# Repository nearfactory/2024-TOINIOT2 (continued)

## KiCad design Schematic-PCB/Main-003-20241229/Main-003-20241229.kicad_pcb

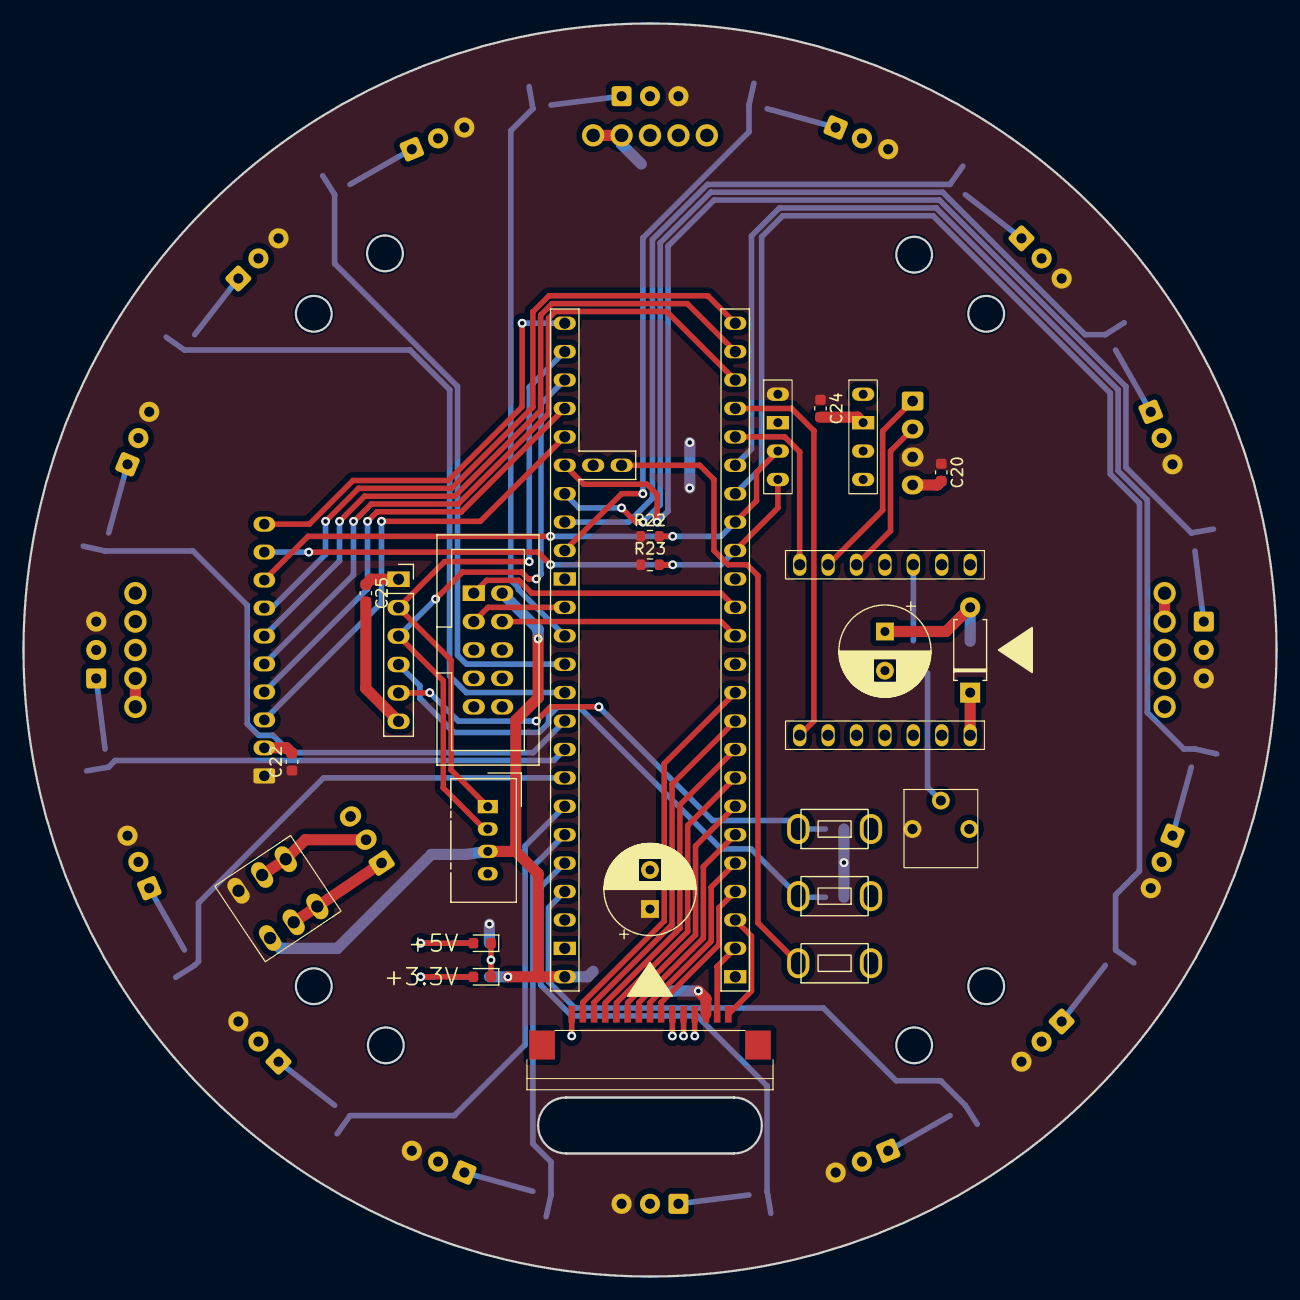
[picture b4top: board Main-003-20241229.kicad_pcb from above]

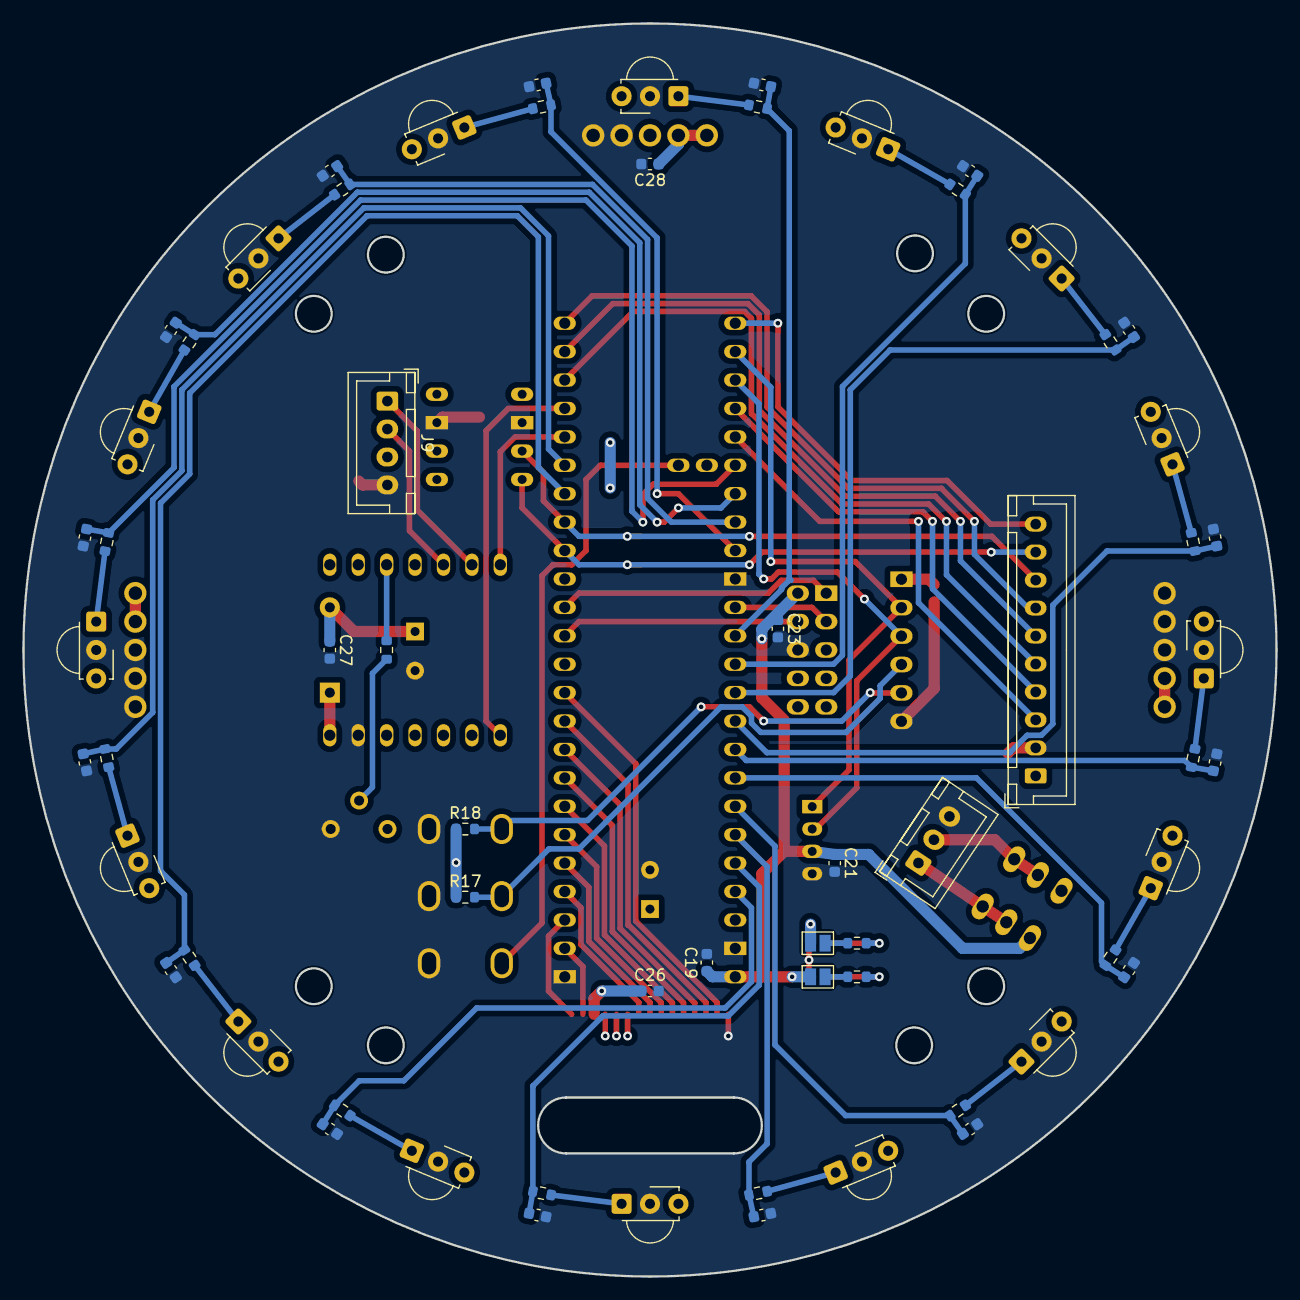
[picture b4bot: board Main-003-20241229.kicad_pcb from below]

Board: 2 copper layers, 112.0 x 112.0 mm, 90 parts (64 on the bottom side), 78 nets.

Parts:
C1, C2, C3, C4, C5, C6, C7, C8, C9, C10, C11, C12, C13, C14, C15, C16: 0.33uF; C_0603_1608Metric
C17, C18: 470uF; CP_Radial_D8.0mm_P3.50mm
C19, C20, C21, C22, C23, C24, C25, C26, C27, C28: 0.1uF; C_0603_1608Metric
D1: PWR-5; LED_0603_1608Metric
D2: PWR-3.3; LED_0603_1608Metric
D3: D_Small; D_A-405_P7.62mm_Horizontal
J1: Conn_PWR; JST_XH_B3B-XH-A_1x03_P2.50mm_Vertical
J2, J3, J4: Conn_NeoPixel; Connector
J5: CamS3-6; PinSocket_1x06_P2.54mm_Vertical
J6: CamS3-4; NS-Tech_Grove_1x04_P2mm_Vertical
J7: Pixy 2.1; IDC-Header_2x05_P2.54mm_Vertical
J8: Conn_MD; 1.0K-FX-15PWB
J9: Conn_Dribbler; JST_XH_B4B-XH-A_1x04_P2.50mm_Vertical
J10: Conn_UI; JST_XH_B10B-XH-A_1x10_P2.50mm_Vertical
JP1, JP2: Jumper_2_Small_Open; SolderJumper-2_P1.3mm_Open_Pad1.0x1.5mm
R1, R2, R3, R4, R5, R6, R7, R8, R9, R10, R11, R12, R13, R14, R15, R16: 39K; R_0603_1608Metric
R17, R18, R21: 10K; R_0603_1608Metric
R19, R20: 330; R_0603_1608Metric
R22, R23: 1K; R_0603_1608Metric
RV1: 10K; 3362P
SW1: Main_RST; TVBP06-B043C
SW2, SW3: Cam_RST; TVBP06-B043C
SW4: SW_DPDT_x2; 2MD1-T2-B4-M2-Q-N
U1, U2, U3, U4, U5, U6, U7, U8, U9, U10, U11, U12, U13, U14, U15, U16: TSSP4038
U17: DEV-16771; MODULE_DEV-16771
U18: BNO055
U19: XIAO ESP32C3

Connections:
3.3V: J1.2, SW4.5 (B), SW4.6 (C)
5.0V: J1.1, SW4.2 (B), SW4.3 (C)
+3.3V: C18.1, C20.1, C22.1, C24.1, C26.1, J8.13, J9.3, J10.1, JP2.2 (B), R17.1, R18.1, R22.1, R23.1, RV1.1, SW4.4 (A), U1.3 (Vs), U2.3 (Vs), U3.3 (Vs), U4.3 (Vs), U5.3 (Vs), U6.3 (Vs), U7.3 (Vs), U8.3 (Vs), U9.3 (Vs), U10.3 (Vs), U11.3 (Vs), U12.3 (Vs), U13.3 (Vs), U14.3 (Vs), U15.3 (Vs), U16.3 (Vs), U18.1 (VIN)
+5V: C17.1, C19.1, C21.1, C23.1, C25.1, C27.1, C28.1, D3.2 (A), J2.1, J2.2, J3.1, J3.2, J4.1, J4.2, J5.1, J6.3, J7.2, JP1.2 (B), SW4.1 (A), U17.VIN
BUZZER: J10.10, U17.33 (MCLK2)
Cam-RX: J5.3, J6.2, U17.35 (TX8)
Cam-TX: J5.2, J6.1, U17.34 (RX8)
Cam_EN: J5.4, R17.2, SW2.2
Cam_G0: J5.5, R18.2, SW3.2
EN-1: J8.2, U17.9 (OUT1C)
EN-2: J8.4, U17.7 (RX2)
EN-3: J8.6, U17.5 (IN2)
EN-4: J8.8, U17.3 (LRCLK2)
EN-D: J9.2, U19.5 (SDA_D4)
GND: C1.2, C2.2, C3.2, C4.2, C5.2, C6.2, C7.2, C8.2, C9.2, C10.2, C11.2, C12.2, C13.2, C14.2, C15.2, C16.2, C17.2, C18.2, C19.2, C20.2, C21.2, C22.2, C23.2, C24.2, C25.2, C26.2, C27.2, C28.2, D1.1 (K), D2.1 (K), J1.3, J2.4, J2.5, J3.3, J3.4, J3.5, J4.3, J4.4, J4.5, J5.6, J6.4, J7.6, J8.1, J9.4, J10.2, RV1.3, SW1.1, SW2.1, SW3.1, U1.2 (GND), U2.2 (GND), U3.2 (GND), U4.2 (GND), U5.2 (GND), U6.2 (GND), U7.2 (GND), U8.2 (GND), U9.2 (GND), U10.2 (GND), U11.2 (GND), U12.2 (GND), U13.2 (GND), U14.2 (GND), U15.2 (GND), U16.2 (GND), U17.GND, U18.2 (GND), U18.7 (GND), U19.13 (GND)
KickerSignal: J8.11, U19.4 (A3_D3)
Line-RX: J8.15, U17.1 (TX1)
Line-TX: J8.14, U17.0 (RX1)
MISO: J7.1, U17.12 (MISO)
MOSI: J7.4, U17.11 (MOSI)
Main-RX7: U17.28 (RX7), U19.7 (TX_D6)
Main-TX7: U17.29 (TX7), U19.8 (RX_D7)
Main_RST: SW1.2, U17.PROGRAM
NeoPixel_PWM: J2.3, U19.11 (MOSI_D10)
unnamed: D1.2 (A), R19.2
unnamed: D2.2 (A), R20.2
unnamed: D3.1 (K), U19.14 (5V)
unnamed: JP1.1 (A), R19.1
unnamed: JP2.1 (A), R20.1
unnamed: R21.1, RV1.2
unnamed: R1.1, U1.1 (OUT)
unnamed: R2.1, U2.1 (OUT)
unnamed: R3.1, U3.1 (OUT)
unnamed: R4.1, U4.1 (OUT)
unnamed: R5.1, U5.1 (OUT)
unnamed: R6.1, U6.1 (OUT)
unnamed: R7.1, U7.1 (OUT)
unnamed: R8.1, U8.1 (OUT)
unnamed: R9.1, U9.1 (OUT)
unnamed: R10.1, U10.1 (OUT)
unnamed: R11.1, U11.1 (OUT)
unnamed: R12.1, U12.1 (OUT)
unnamed: R13.1, U13.1 (OUT)
unnamed: R14.1, U14.1 (OUT)
unnamed: R15.1, U15.1 (OUT)
unnamed: R16.1, U16.1 (OUT)
PH-1: J8.3, U17.8 (TX2)
PH-2: J8.5, U17.6 (OUT1D)
PH-3: J8.7, U17.4 (BCLK2)
PH-4: J8.9, U17.2 (OUT2)
PH-D: J9.1, U19.6 (SCL_D5)
SCK: J7.3, U17.13 (SCK)
SCL: J10.9, R23.2, U17.24 (A10), U18.4 (SCL/R)
SDA: J10.8, R22.2, U17.25 (A11), U18.3 (SDA/T)
SW-TAC-1: J10.4, U17.36 (CS2)
SW-TAC-2: J10.5, U17.30 (CRX3)
SW-TAC-3: J10.6, U17.31 (CTX3)
SW-TAC-4: J10.7, U17.32 (OUT1B)
SW-TOG: J10.3, U17.37 (CS3)
Volume: R21.2, U19.3 (A2_D2)
ball01: C1.1, R1.2, U17.14 (A0)
ball01k: J8.10, U19.1 (A0_D0)
ball02: C2.1, R2.2, U17.15 (A1)
ball02k: J8.12, U19.2 (A1_D1)
ball03: C3.1, R3.2, U17.16 (A2)
ball04: C4.1, R4.2, U17.17 (A3)
ball05: C5.1, R5.2, U17.18 (A4)
ball06: C6.1, R6.2, U17.19 (A5)
ball07: C7.1, R7.2, U17.20 (A6)
ball08: C8.1, R8.2, U17.21 (A7)
ball09: C9.1, R9.2, U17.22 (A8)
ball10: C10.1, R10.2, U17.23 (A9)
ball11: C11.1, R11.2, U17.26 (A12)
ball12: C12.1, R12.2, U17.27 (A13)
ball13: C13.1, R13.2, U17.38 (A14)
ball14: C14.1, R14.2, U17.39 (A15)
ball15: C15.1, R15.2, U17.40 (A16)
ball16: C16.1, R16.2, U17.41 (A17)

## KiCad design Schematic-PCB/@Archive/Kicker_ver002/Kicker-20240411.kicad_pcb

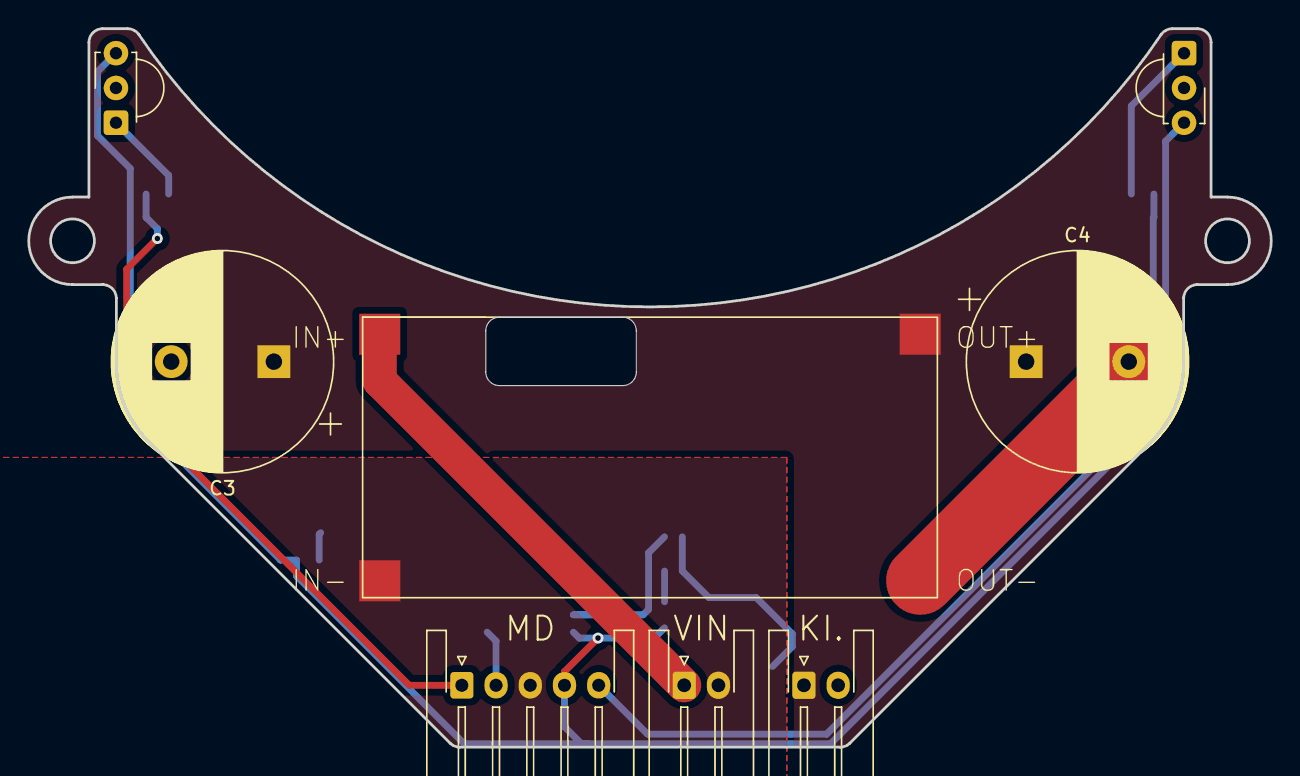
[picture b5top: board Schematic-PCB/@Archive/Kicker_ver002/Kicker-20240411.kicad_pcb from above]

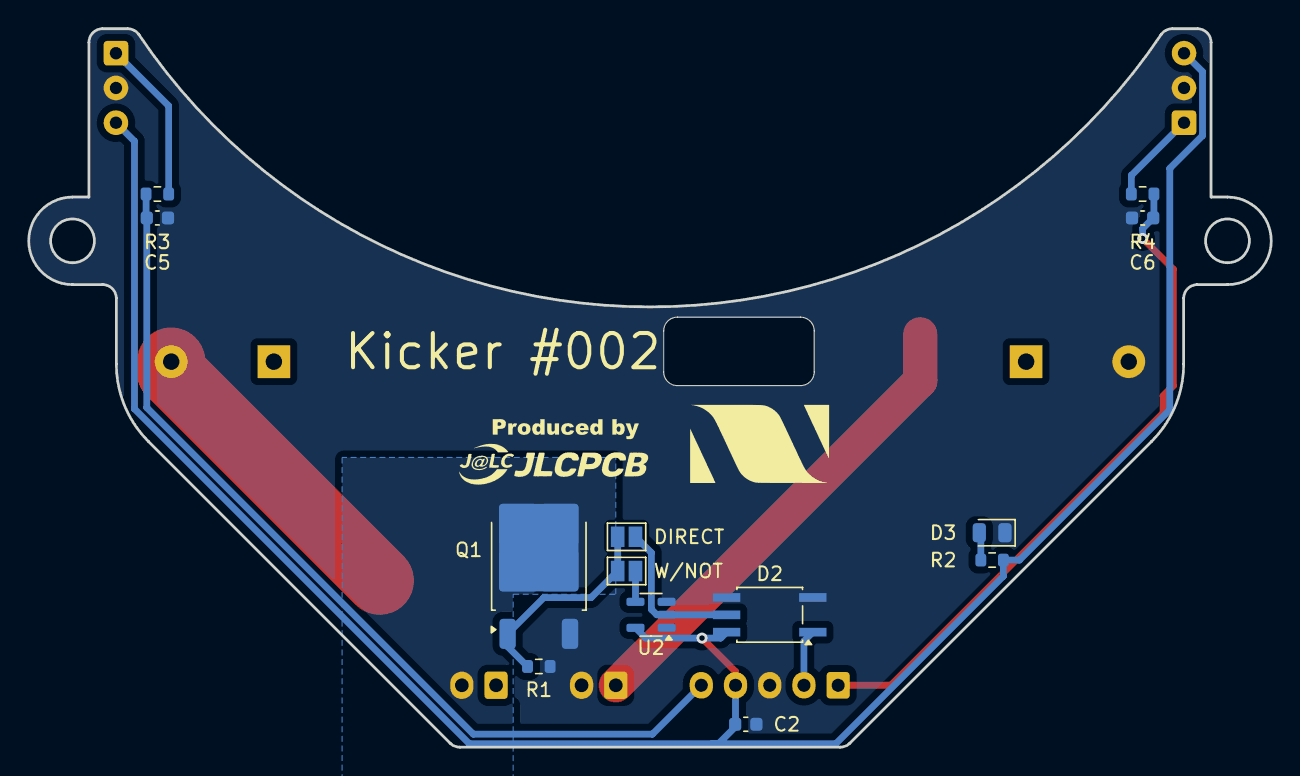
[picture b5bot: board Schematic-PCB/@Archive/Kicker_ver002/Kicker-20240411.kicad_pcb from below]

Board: 2 copper layers, 90.8 x 52.5 mm, 21 parts (13 on the bottom side), 14 nets.

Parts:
C2: 0.1uF; C_0603_1608Metric
C3, C4: 2200uF; CP_Radial_D16.0mm_P7.50mm
C5, C6: 0.33u; C_0603_1608Metric
D2: SO-5_4.4x3.6mm_P1.27mm
D3: PWR; LED_0805_2012Metric
DIRECT: Jumper_2_Small_Open; SolderJumper-2_P1.3mm_Open_Pad1.0x1.5mm
KI.: Conn_01x02_Pin; JST_XH_S2B-XH-A-1_1x02_P2.50mm_Horizontal
MD: Conn_01x05_Pin; JST_XH_S5B-XH-A-1_1x05_P2.50mm_Horizontal
Q1: NMOS; TO-252-2
R1: 10K; R_0603_1608Metric
R2: 330; R_0603_1608Metric
R3, R4: 39K; R_0603_1608Metric
U1: XL6009-SMD
U2: 74LVC1G04; SOT-23-5
U3, U4: TSSP58P38; Vishay_MINICAST-3Pin
VIN: Conn_01x02_Pin; JST_XH_S2B-XH-A-1_1x02_P2.50mm_Horizontal
W/NOT: Jumper_2_Small_Open; SolderJumper-2_P1.3mm_Open_Pad1.0x1.5mm

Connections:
+3.3V: C2.1, D2.6 (VCC), MD.4, R2.1, U2.5 (VCC), U3.3 (Vs), U4.3 (Vs)
GND: C2.2, C3.2, C4.2, C5.2, C6.2, D2.3 (Cathode), D2.4 (GND), D3.1 (K), MD.3, Q1.3 (S), R1.2, U1.2 (-IN), U1.4 (-OUT), U2.3 (GND), U3.2 (GND), U4.2 (GND), VIN.2
KickerPower: C3.1, C4.1, KI..1, U1.3 (+OUT)
KickerSignal: D2.5 (VO), DIRECT.1 (A), U2.2
KickerSignal-main: D2.1 (Anode), MD.2
unnamed: D3.2 (A), R2.2
unnamed: KI..2, Q1.2 (D)
unnamed: DIRECT.2 (B), Q1.1 (G), R1.1, W/NOT.2 (B)
unnamed: U2.4, W/NOT.1 (A)
unnamed: R3.1, U3.1 (OUT)
unnamed: R4.1, U4.1 (OUT)
VCC: U1.1 (+IN), VIN.1
ball01k: C5.1, MD.5, R3.2
ball02k: C6.1, MD.1, R4.2

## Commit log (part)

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2024-11-08 update: メイン基板を開いた
2024-11-08 update: ラインセンサのテストプログラムを更新した
2024-11-08 add: ラインセンサのアーカイブを追加した
2024-11-09 add: 回路のアーカイブを追加した
2024-11-10 update: ラインセンサの動作確認をした
2024-11-10 update: メイン基板のPCBを更新した
    ボタンをSMD→THTに変更
    FPCコネクタを裏面に配置
    発注用ファイルを出力
2024-11-10 update: ボール追従プログラムを更新
2024-11-10 add: ボールセンサの値を視覚化するやつを追加
2024-11-10 update: メイン基板の穴を削除した
2024-11-11 update: ラインセンサ基板などを開いてピンアサインを確認した
2024-11-11 update: ボールセンサの角度算出プログラム更新
2024-11-11 add: モジュール単位でライブラリ化した
    ちょっとずつ進める
2024-11-12 update: ラインセンサ基板を開いた
2024-11-12 update: UI基板を開いた
2024-11-12 update: メイン基板のシルクスクリーンを更新した
2024-11-12 update: 電源基板のラインセンサ向け供給コネクタをVHコネクタからXHコネクタに変更した
2024-11-12 add: 電源基板の3Dモデルを出力した
2024-11-12 update: UI基板のボタンの1つが+3.3Vに接続されていなかったのを修正した
2024-11-12 UI基板の各ボタンにチャタリング防止用コンデンサを配置した
    ただしトグルスイッチを除く()
2024-11-13 add: モーターピン保護部品の3Dプリンタ印刷用ファイルを追加
2024-11-13 update: TeensyとAtMega2560のUART通信をできるようにした
2024-11-13 update: MD基板を開いてNchMOSFETのピンアサインを確認した
2024-11-13 update: メイン基板とNeoPixel基板の発注用ファイルを出力したりした
    NeoPixel基板はコネクタを1コ→3コに増やした
2024-11-14 update: 取りあえず動くやつ
2024-11-14 add: ラインセンサ基板の実験をした
2024-11-14 update: Teensy-AtMega間の通信を確立した
    ズレない
2024-11-14 update: MD基板のNchMOSFET部分の設計を修正した
    ピンアサインも確認したから大丈夫だと思う
2024-11-14 add: メイン基板の新しいプロジェクトファイルを追加
2024-11-15 update: ボーレートを更新
2024-11-15 update: 簡易的な白線避けをできるようにした
2024-11-15 add: maxonモーター用ブラケットのちょっと地面に近くなるバージョンを追加した
2024-11-15 add: FPCケーブルの反転バージョンを追加した
2024-11-15 update: メイン基板を開いたりしてピンアサインを確認した
2024-11-15 update: ラインセンサの読み込みをライブラリ化した
2024-11-15 update: MD基板をメイン基板に合わせたFPCコネネクタのピンアサインに変更した
    DRよろしく
2024-11-15 update: FPCケーブル（旧）を裏表導通するように変更した
2024-11-15 add: モーターの制御周りをライブラリ化した
2024-11-16 update: MD#003 / UI#004 のDRをした
2024-11-16 update: ライブラリ化の動作確認をした
2024-11-16 update: 白線避けプログラムを更新した
2024-11-16 add: モーターブラケットの新規印刷ファイルを追加した
2024-11-16 add: オムニホイールR55の印刷用ファイルを追加した
2024-11-16 add: ボールセンサの処理をライブラリ化
2024-11-16 add: 地磁気をライブラリ化
2024-11-16 update: ボールセンサをグラフ表示するやつを更新
2024-11-16 update: ボール追従プログラムを更新した
2024-11-17 update: MD基板の発注用ファイルの更新版を再度出力した
2024-11-19 add: digikeyロゴのデータを追加
2024-11-19 add: 名刺の発注用データを追加した
2024-11-19 update: UIをライブラリ化した
2024-11-19 update: ディスプレイをライブラリ化した
2024-12-03 update: ボール角度算出
2024-12-03 add: オムニホイールのCNC切削用ファイルを追加した
    DXFのほうね
2024-12-03 update: ボールの角度計算を更新した
    なんやかんやで最大値の左右3つが安定する
2024-12-03 add: ボールセンサカバーの3Dプリンタ印刷用ファイルを追加した
2024-12-03 update: 回り込みプログラムを更新した
2024-12-04 update: アナログピンの配置を確認した
2024-12-04 add: オムニホイールの3Dプリンタ印刷用ファイルを追加した
2024-12-04 add: ボールセンサのテストをした
2024-12-04 update: 回り込みのプログラムを更新した
2024-12-05 add: オムニホイールの3Dプリンタ用印刷ファイルを追加した
2024-12-05 update: 回り込みのプログラムを更新した
    7~8割の確率で完璧に捉えられるようになった
2024-12-05 update: ディスプレイのプログラムを更新
    ラインセンサ・任意の変数を表示&値を変更できるようにした
2024-12-06 add: ドリブラー用部品の3Dプリンタ印刷用ファイルを追加
2024-12-06 add: ドリブラー部品の3Dプリンタ印刷用ファイルを追加した
2024-12-07 update: アタッカーのプログラムを更新した
2024-12-08 update: 新機体のプログラムを更新した
2024-12-09 update: 外側のラインセンサのアルゴリズムを変更した
2024-12-09 add: ドリブラー用部品の3Dプリンタ印刷用ファイルを追加した
2024-12-09 update: 白線を半分以上跨いでも戻れるようにした(理論上)
2024-12-10 update: ラインセンサのプログラムを更新した
2024-12-10 update: 新機体のプログラムを更新した
    地磁気でラインよけ
2024-12-10 add: ドリブラー関連部品の3Dプリンタ印刷用ファイルを追加した
2024-12-10 add: 旧機体用オムニホイールの設計修正版の3Dプリンタ印刷用ファイルを追加した
2024-12-11 add: オムニホイール更新版の3Dプリンタ印刷用ファイルを追加した
2024-12-11 add: ドリブラー用部品の3Dプリンタ印刷ファイルを追加した
2024-12-11 add: Pixy2.1用のカメラサポーターを設計して3Dプリンタ印刷用ファイルを追加した
2024-12-11 add: ドリブラー部品の3Dプリンタ印刷用ファイルとCNC切削用ファイルを追加した
2024-12-14 update: メインマイコンのピンを修正した
2024-12-14 add: 旧機体のプログラムを追加した
2024-12-14 add: モーターのテストプログラムを追加した
2024-12-14 add: 音羽のプログラム追加用フォルダを作成
2024-12-14 update: 旧機体のプログラムを更新した
2024-12-14 add: カメラ・ミラー台の寸法変更（PixyのUSBケーブルが刺さるようにした）
2024-12-14 update: FPCケーブルのPCBデザインを修正した
    裏面のベタを削除して各個独立した配線になるようにした
2024-12-14 remove: フォルダ作成用のgitkeepファイルを削除
2024-12-15 update: 音羽のプログラムを解読した
2024-12-15 update: 新機体のピンアサインなどを修正した
2024-12-15 update: いろいろなKiCadファイルを開いた
2024-12-16 add: update: fix: remove:
2024-12-16 update: モーターのテストプログラムを更新した
2024-12-16 add: Main基板ver.003のファイルを作成・中身を更新した
    原本はver.002だけど、コネクタの種類がFPCじゃなくなってるよ
2024-12-17 add: 3Dプリンタ印刷用ファイルとCNC切削用ファイルを追加
2024-12-17 update: メイン基板ver.003 を更新した
    キッカー用5ピンも配置した
    DRは一通りやったけどそっちでも1回やってみてほしい
2024-12-17 update: メイン基板ver.003のDRをした
    特に問題は見つからなかった
2024-12-18 update: メインとMDの基板を編集
2024-12-19 update: ボールを保持しているかの判断・突進をできるようにした
2024-12-19 update: ラインセンサのプログラムを更新した
    delay()を3ms以下にするとうまくdigitalRead()できない
2024-12-19 add: キッカー ver.002 のアーカイブを追加した
2024-12-19 update: キッカーのテストプログラムを更新した
2024-12-20 update: 白線から出にくくした
2024-12-20 update: キッカーを使えるようにした
    はやい つよい
2024-12-20 update: カメラの通信速度を早くした
2024-12-20 update: ゴールの方を向けるようにした
2024-12-21 add: ラインセンサ基板の外形の更新版を追加
2024-12-21 オムニホイールの出力用ファイルを修正した
2024-12-21 add: トップマーカーの3Dプリンタ印刷用ファイルを追加した
2024-12-21 add: 鏡面台の更新版の3Dプリンタ印刷用ファイルを追加
2024-12-21 add: 電池固定用部品の更新版の3Dプリンタ印刷用ファイルを追加
2024-12-21 update: 前後左右の外側ラインセンサに対して避ける動きを設定した
2024-12-21 update: 白線避けを更新した
2024-12-21 update: 現状のボタン数でゲイン調整などをできるようにした
2024-12-21 update: ボールを保持した後、ゴールの方向に移動するようにした
2024-12-21 update: シュート・キックの動作を見直した
2024-12-21 update: 回り込み中に白線に繰り返し触れた場合、ボールに直進するようにした
2024-12-21 Auto stash before merge of "main" and "origin/main"
2024-12-22 update: ゴールに向かえるようにした
2024-12-22 update: 和歌山ノード用のプログラムを更新した
2024-12-22 add: 3Dプリント発注用ファイル（上段のみ）を追加
2024-12-22 add: ラインセンサ基板 ver.003 を追加した
    今後はこのプロジェクトフォルダをいじっていっていこう
2024-12-23 add: 関西ブロック用のプログラムを追加した
2024-12-24 バッテリー保護用部品の3Dプリンタ印刷用ファイルを追加
2024-12-24 add: バッテリー保護用部品の3Dプリンタ印刷用ファイルを追
2024-12-24 update: 関西大会用のプログラムをキレイにした
2024-12-24 add: メイン-ラインの通信テストプログラムを更新した
2024-12-24 add: FPC ver.004 のファイルを追加した
2024-12-24 update: メイン - ラインのの通信テストプログラムを追加した
2024-12-24 update: しきい値を2つ使うようにした
2024-12-24 update: FPC ver.004 に更新した
    プロジェクトファイル自体は一番初めのモノを使用してるよ
2024-12-24 add: ドリブラー基板 ver.002 のプロジェクトファイルを追加
2024-12-24 update: ラインセンサ基板 ver.003の回路図を更新した
    使ってないからbuzzerいらない？
2024-12-25 update: ブザーをけした
2024-12-25 add: 鏡面台の3Dプリンタ印刷用ファイルを追加した
2024-12-25 add: ボディ外注用の3Dプリンタ印刷用ファイルを追加した
2024-12-25 update: ラインセンサ基板の回路図を更新した
    DRおねがい
2024-12-25 update: ラインセンサ基板 ver.003 の回路図を編集・更新した
2024-12-25 update: ライントレースのテストプログラムを更新した
2024-12-25 add: Pixy2.1台の更新版の3Dプリンタ印刷用ファイルを追加した
2024-12-25 update: ラインセンサ基板 ver.003 を更新した
    回路図のDRをした
    いろいろ問題点ありそうだから、明日もう一回DRし直してからPCBいこか
    出来れば明日、無理なら明後日ぐらいまでに必ず完成させよう！！
2024-12-26 update: 常にゴールの方向を向けるようにした
    中立点からほぼ入るようになった
2024-12-26 add: ラインセンサ基板 ver.003を更新した
    あと3Dプリンタ印刷用ファイルも追加した
2024-12-26 update: ラインセンサ基板の回路とPCBを更新した
    閾値用PWMの周波数選択用のジャンパの削除
    基板外形の更新
    など
2024-12-26 update: ラインセンサ基板の基板外形を更新した
2024-12-26 update: ラインセンサ基板のPCBを更新した
    部品配置はひととおりやったから配線を頼む
    配線難しかったり逆に基板外形が大きすぎたらまた連絡して
2024-12-26 add: 外注用のボディの3Dプリンタ印刷用ファイルを追加
2024-12-26 add: ボディの外注用3Dプリンタ印刷用ファイルの更新版を追加した
2024-12-27 update: ラインセンサ基板のPCBを更新した
    配線を進めた
    Thをベタ化して配線を楽にした
2024-12-27 update: とりあえずラインセンサ基板の配線を終わらせた
2024-12-28 update: ラインセンサ基板の1次DRを完了させ、発注用ファイルを出力した
2024-12-28 update: ラインセンサ基板の2次DRを完了させた
2024-12-28 update: 故障復帰用のタイマーを追加した
2024-12-28 Create commit
2024-12-28 GKT1 by010
2024-12-28 remove: FPCケーブルの必要ないプロジェクトフォルダを削除した
    混乱のもとなので...
2024-12-28 add: ちゃんとしたFPCケーブルのバージョンを追加
2024-12-28 update: FPCケーブルの補強材に関する注釈をつけて発注用ファイルを作成した
    次回発注があるならこれを使うかもしれない
    ただしケーブル本体の長さに関しては要確認（補強材の長さを考えてないため）
2024-12-29 update: 移動用の関数を追加した
2024-12-29 update: 音羽のプログラムのフォルダ名を更新した
2024-12-29 貝尻にお願いするファイルを作成
2024-12-30 update: メイン基板のPCBを更新した
2024-12-30 add: 関西ブロック大会用のプレゼンシート(仮)を追加
2024-12-31 update: フォルダ名を変更した
2024-12-31 update: モーターの制御ライブラリを更新した
2024-12-31 update: 守り機体のライブラリを置き換えた
2024-12-31 update: 守り機体のプログラムを更新した
    あとはライントレースを書くだけで一旦完成
2025-01-01 update: 守り機体のプログラムを更新した
2025-01-03 add: CNC切削用のDXFファイルを追加
    ボディの1段目・2段目前・2段目後ろ
2025-01-03 add: ボディカバーなどの3Dプリンタ部品の印刷用ファイルを追加した
2025-01-04 update: 通信のテストプログラムを更新した
2025-01-04 add: 3Dプリンタ印刷用ファイルを追加
2025-01-04 update: サブマイコンのプログラムを更新した
2025-01-05 add: 新機体1用のボールセンサカバーの3Dプリンタ印刷用ファイルを追加
2025-01-05 add: メイン - サブのテストプログラムを追加した
2025-01-05 update: テストプログラムを更新した
2025-01-05 add: MD.ver003 のアーカイブを追加した
2025-01-05 pololu用のモーターブラケットの3Dプリンタ印刷用ファイルを追加した
2025-01-05 add: ラインセンサ(単体)のテストプログラムを追加した
2025-01-05 add: ピンアサイン表を追加した
2025-01-05 update: アタッカーのステートマシンを更新した
2025-01-06 update: ボールを保持したかをある程度見れるようにした
2025-01-06 update: カメラのバグを修正した
2025-01-06 update: プレゼンシートの画像を差し替えた
2025-01-06 update: キッカー基板の回路図を修正した
    ツェナーダイオードをなくした
    +48V-+VDD関連のNchMOSFETのロジックを削除した
2025-01-07 update: ボールが見えないときに下がるようにした
2025-01-07 オムニホイールの3Dプリンタ印刷用ファイルを追加した
    印刷速度を3/4にして層ずれを減らすように頑張ってもらう
2025-01-08 update: ボール保持の判定を更新した
2025-01-08 update: 角度計算のバグを修正した
2025-01-08 update: アタッカーのプログラムを更新した
    いいかんじ
2025-01-08 update: アタッカー更新
2025-01-08 update: キーパーのライブラリを更新した
2025-01-08 update: 白線の処理を更新した
2025-01-08 update: キーパーの白線の処理を更新した
2025-01-08 add: オムニホイールのCNCと3Dプリンタ用ファイルを追加
2025-01-09 add: 設計を見直したボールセンサカバーの3Dプリンタ印刷用ファイルを追加
2025-01-09 add: モーターブラケットの更新版の3Dプリンタ印刷用ファイルを追加
2025-01-10 update: 低速だがライントレースできるようにした
2025-01-10 update: 押し出されても戻れるようにした
2025-01-10 update: ゴール端で止まるようにした
2025-01-10 update: キーパーのプログラムを更新した
2025-01-10 新機体2用のバッテリーケース・フタの3Dプリンタ印刷用ファイルを出力した
2025-01-11 update: アタッカーの白線の処理をディフェンスと統一した
2025-01-11 update: ラインセンサのプログラムを更新した
    とりあえずしきい値は固定
2025-01-11 update: 白線避け更新
2025-01-11 add: カメラ台の3Dプリンタ印刷用ファイルを追加した
2025-01-11 update: 白線よけを更新した
2025-01-11 update: アタッカーのプログラムを更新した
    動画の通り
2025-01-11 Create 2024_OldDefender_otowa7_T2_a8
2025-01-11 Create a
2025-01-11 update: アタッカーのプログラムを更新した
    解説してて気づいたところ
2025-01-11 update: 回り込み中にゴールに向ける条件を変更した
2025-01-11 GK by010最新版ver.9
2025-01-11 update: 押し込みを実装した
2025-01-11 update: 押し込みに遷移するときのバグを修正した
2025-01-12 update: 更新
2025-01-15 update: キッカー基板の回路図を開きなおした
2025-01-15 add: ラインセンサ基板ver.004のKiCadプロジェクトを作成した
2025-01-15 update: ラインセンサ基板 ver.004 のフットプリントとPCBを編集した
2025-01-16 update: MD基板 ver.005 のPCBを更新した
    ラインセンサとのコネクタ・キッカー基板とのコネクタ・メイン基板とのコネクタ・UARTレベル変換用のMOSFETを追加する必要あり
2025-01-16 update: MD基板 ver.005 を更新
2025-01-17 update: conflictをresolve
2025-01-21 add: バッテリーカバーなどの3Dプリンタ印刷ファイルを追加
2025-01-21 add: オムニホイールの3Dプリンタ印刷用ファイルを追加
2025-01-21 add: リツモリ用のプログラムを追加した
2025-01-23 clean: ファイル名を変更した
2025-01-23 clean: カメラの3Dプリンタ印刷用ファイルの名前を変更した
2025-01-23 add: カメラ台の3Dプリンタ印刷用ファイルを追加
2025-01-23 add: ハンドルの3Dプリンタ印刷用ファイルを追加した
2025-01-23 add: 新機体-2の外側カバーの3Dプリンタ印刷用ファイルを追加した
2025-01-24 update: 回り込みを改善した
2025-01-24 update: 敵よけを更新した
2025-01-24 add: 電源基板保護部品の3Dプリンタ印刷用ファイルを追加した
2025-01-27 add: 新機体-02用のバッテリーケースの3Dプリンタ印刷用ファイルを追加した
2025-01-27 add: 新機体-02の前方カバーの3Dプリンタ印刷用ファイルを追加
2025-01-27 update: モーター/キッカー/UIのテストプログラムを更新した
2025-01-29 update: キッカープログラムを更新
2025-01-29 update: ラインセンサ基板の発注用データなどを出力し直した
2025-01-30 update: ラインセンサ基板のArduino Mega 2560 Pro Board のフットプリントを変更した
2025-01-30 update: キッカープログラムを更新した
2025-01-30 add: ラインセンサ基板のArduinoMega2560ProBoardの更新版のフットプリントに合わせた発注用ファイルを追加
2025-02-03 add: 1000万3Dプリンタ用の印刷用ファイルを追加
2025-02-03 update: キッカーのテスト用プログラムを更新した
2025-02-04 add: NeoPixelのテストプログラムを新規追加した
2025-02-07 update: pololu用に色々変更した
    1番モーターだけ向きが違う
2025-02-12 update: ドリブルの動作を変更した
2025-02-15 update: 家用に速度を落とした
2025-02-16 update: ディスプレイ上で敵よけを考えた
2025-02-16 update: 敵避け
2025-02-18 update: 敵避け・押し込み
2025-02-19 update: モーターの回転方向を修正した
2025-02-19 update: ラインセンサのバグを修正した
    キーパーやるまで全く気づかなかった
2025-02-19 update: とりあえずライントレース
2025-02-21 update: ライントレースを更新した
2025-02-21 update: アタッカーがゴールの方向を向く条件を変更した
2025-02-21 update: ボールの前で停まるようにした
2025-02-21 update: キーパーダッシュに遷移する条件を変更した
2025-02-22 update: ボールがないときに中央に戻るようにした
2025-02-22 update: 中立点のボールを押し出すようにした
2025-02-22 update: 故障復帰のときにボールを避けるようにした
2025-02-22 update: 反対側のポケットに回り込むようにした
2025-02-22 update: キーパーダッシュに遷移する条件を厳しくした
2025-02-22 update: キーパーが動かなくなるバグを修正した
    0除算
2025-02-22 update: キーパーを色々修正した
2025-02-22 update: 押し合いの動作を追加した
    あんまりうまくいかない
2025-02-23 update: リツモリ用にボールのしきい値などを調整した
2025-02-23 update:
2025-02-23 update: あ
2025-02-23 update: edge
2025-02-28 add: ラジコン用のプログラムを追加した
2025-02-28 update: 双方向通信できるようにした
2025-02-28 update: ラジコンでキッカーを動かせるようにした
2025-03-09 add: コントローラー用のデスクトップアプリケーションを追加した
2025-03-09 update: ライブラリ化
2025-03-09 add: SImpleBLE
2025-03-10 add: 動くサンプルを見つけた
2025-03-10 add: C#
    https://qiita.com/gpsnmeajp/items/04572aa087ab8ae1bd06
2025-03-11 add: スキャンできるようにした
2025-03-11 update: スキャンまでを組み込んだ
2025-03-12 update: ESP32C3のキャラクテリスティックを全て取得できるようにした
2025-03-12 update: PCから送れるようにした
2025-03-12 update: 色々関数化した
2025-03-13 update: コントローラーの情報を送れるようにした
2025-03-13 saved UNDO information for reset changes and discarded files
2025-03-13 update: 落ちないようにした
    0除算
2025-03-13 update: 角度を操作できるようにした
2025-03-14 update: ラジコン完全版
2025-04-06 update: いろいろ
2025-04-07 update: 色々
